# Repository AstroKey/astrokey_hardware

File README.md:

# astrokey_hardware
AstroKey hardware repository

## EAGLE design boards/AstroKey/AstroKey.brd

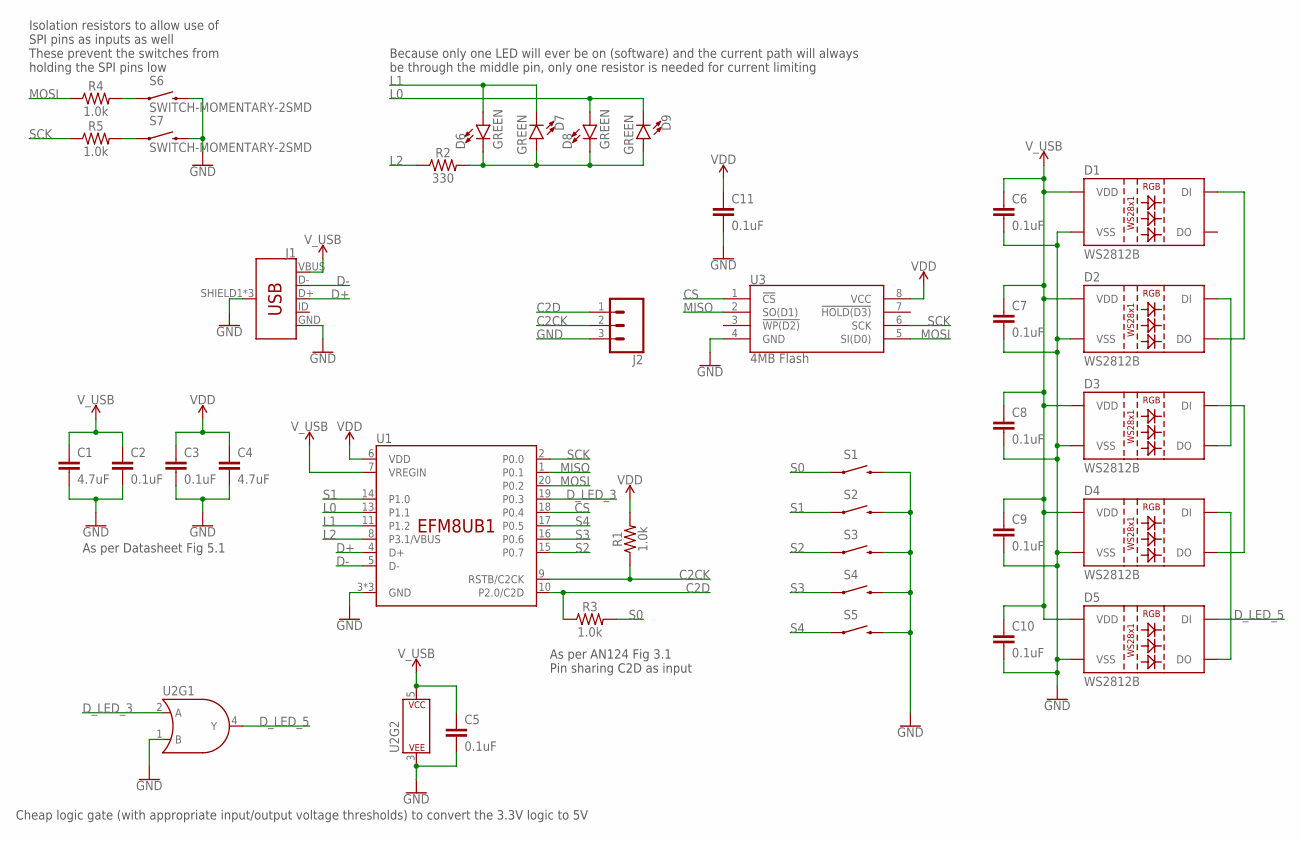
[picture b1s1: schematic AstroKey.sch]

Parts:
C1, C4: 4.7uF; 0402
C2, C3, C5, C6, C7, C8, C9, C10, C11: 0.1uF; 0402
D1, D2, D3, D4, D5: WS2812B
D6, D7, D8, D9: GREEN; LED-0603
J1: USB_MICRO-B_FEMALE-SMT; USB-B-MICRO-SMD
J2: CONN_031X03_NO_SILK; 1X03_NO_SILK
R1, R3, R4, R5: 1.0k; 0402
R2: 330; 0402
S1, S2, S3, S4, S5: MOMENTARY-SWITCH-SPST-SOCKET-SMD-CHERRY; CHERRY-MX-SOCKET
S6, S7: SWITCH-MOMENTARY-2SMD; TACTILE-SWITCH-SMD
U1: EFM8UB1; SILABS-QFN20
U2: 74AHC1G32GW; SOT353; PARTNO MC74VHC1GT32
U3: 4MB Flash; SO08

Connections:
C2CK: J2.2, R1.1, U1.9 (RSTB/C2CK)
C2D: J2.1, R3.1, U1.10 (P2.0/C2D)
CS: U1.18 (P0.4), U3.1 (!CS)
D+: J1.D+, U1.4 (D+)
D-: J1.D-, U1.5 (D-)
D_LED_3: U1.19 (P0.3), U2.2 (A)
D_LED_5: D5.4 (DI), U2.4 (Y)
GND: C1.2, C2.2, C3.2, C4.2, C5.2, C6.2, C7.2, C8.2, C9.2, C10.2, C11.2, D1.3 (VSS), D2.3 (VSS), D3.3 (VSS), D4.3 (VSS), D5.3 (VSS), J1.GND, J1.SHIELD1 (SHIELD), J1.SHIELD2 (SHIELD), J1.SHIELD3 (SHIELD), J2.3, S1.2, S2.2, S3.2, S4.2, S5.2, S6.3 (2), S7.3 (2), U1.3 (GND), U1.12 (GND), U1.21 (GND), U2.1 (B), U2.3 (P$V-), U3.4 (GND)
L0: D6.A, D7.C, U1.13 (P1.1)
L1: D8.A, D9.C, U1.11 (P1.2)
L2: R2.1, U1.8 (P3.1/VBUS)
MISO: U1.1 (P0.1), U3.2 (SO(D1))
MOSI: R4.1, U1.20 (P0.2), U3.5 (SI(D0))
unnamed: D4.4 (DI), D5.2 (DO)
unnamed: D6.C, D7.A, D8.C, D9.A, R2.2
unnamed: D3.4 (DI), D4.2 (DO)
unnamed: D2.4 (DI), D3.2 (DO)
unnamed: D1.4 (DI), D2.2 (DO)
unnamed: R4.2, S6.1
unnamed: R5.2, S7.1
S0: R3.2, S1.1
S1: S2.1, U1.14 (P1.0)
S2: S3.1, U1.15 (P0.7)
S3: S4.1, U1.16 (P0.6)
S4: S5.1, U1.17 (P0.5)
SCK: R5.1, U1.2 (P0.0), U3.6 (SCK)
VDD: C3.1, C4.1, C11.1, R1.2, U1.6 (VDD), U3.8 (VCC)
V_USB: C1.1, C2.1, C5.1, C6.1, C7.1, C8.1, C9.1, C10.1, D1.1 (VDD), D2.1 (VDD), D3.1 (VDD), D4.1 (VDD), D5.1 (VDD), J1.VBUS, U1.7 (VREGIN), U2.5 (P$V+)

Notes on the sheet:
As per AN124 Fig 3.1 Pin sharing C2D as input
As per Datasheet Fig 5.1
Cheap logic gate (with appropriate input/output voltage thresholds) to convert the 3.3V logic to 5V
Because only one LED will ever be on (software) and the current path will always be through the middle pin, only one resistor is needed for current limiting
Isolation resistors to allow use of SPI pins as inputs as well These prevent the switches from holding the SPI pins low

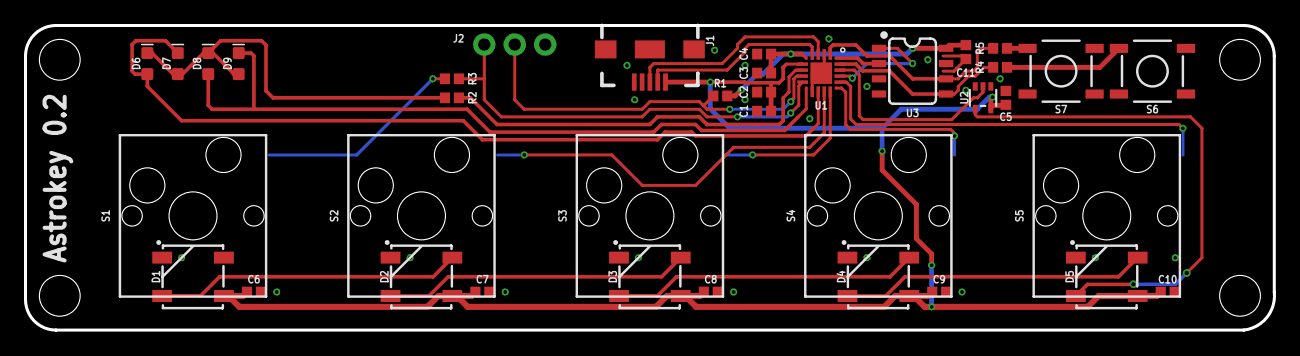
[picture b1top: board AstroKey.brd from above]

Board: 2 copper layers, 104.2 x 25.4 mm, 37 parts (0 on the bottom side), 28 nets.

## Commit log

2017-09-29 Set up eagle directory structure
2017-10-24 Initial board layout done, traces unrouted
2017-10-27 Finished first version of board
2017-12-17 Uploaded Eagle cam file for gerber generation
2018-01-28 Board revision 0.2
    Changed board shape
    Added screw holes to board corners
    Moved USB connector to top of board
    Added SPI Flash IC
    Changed keyswitch footprint to use sockets
    Added layer LEDs and buttons
2018-01-28 Connected CS pin to MCU (no revision number increment)
2018-01-28 Fixed error in comment in schematic
2018-01-28 Aligned C1 with C2 C3 C4 (no revision number increment)
2018-01-28 Fixed part number of OR gate
2018-02-03 Fixed label positions on L0 and L1 nets

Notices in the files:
parts and their libraries:
SparkFun-Capacitors: Licensing: Creative Commons ShareAlike 4.0 International - https://creativecommons.org/licenses/by-sa/4.0
